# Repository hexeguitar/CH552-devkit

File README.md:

# CH552 devkit

### CH552 development board with hardware reboot into bootloader feature.  

### Reboot circuit  

Pressing and releasing the BOOTLOADER button will cycle the power and start the MCU with 1k pull-up on the USB-P line. This will start the built in USB/Serial bootoader. External BOOT input is provided for triggering via DTR or other active low signal.  

Take a look here for similar circuit for the CH559 series:  
https://github.com/hexeguitar/CH55x-HW-reboot  

Python programming script for both USB and serial port can be found here:  
https://github.com/hexeguitar/CH55x_python_flasher  
___
(c) 11.2020 by Piotr Zapart  
www.hexefx.com

[pic1]: pics/ch552_devkit1.jpg "CH552 devkit"
[pic2]: pics/ch552_devkit2.jpg "CH552 devkit"

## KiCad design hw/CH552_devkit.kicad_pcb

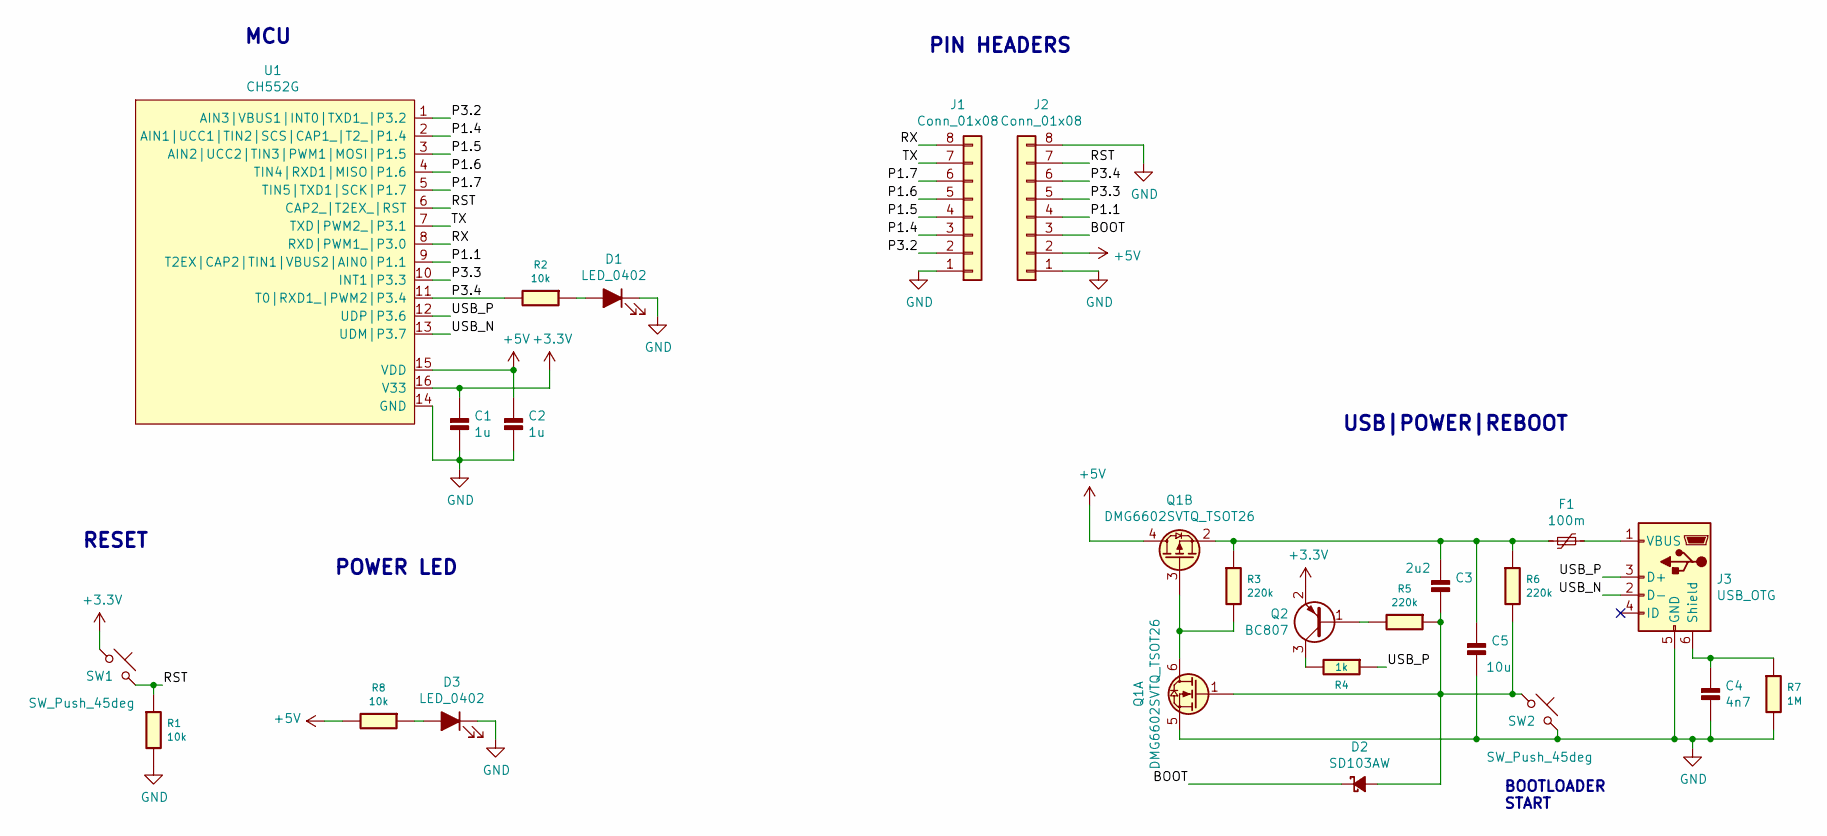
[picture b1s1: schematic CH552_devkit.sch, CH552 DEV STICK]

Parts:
C1, C2: 1u; Hx_C_0805_2012Metric
C3: 2u2; Hx_C_0805_2012Metric
C4: 4n7; Hx_C_0805_2012Metric
C5: 10u; Hx_C_0805_2012Metric
D1, D3: LED_0402; LED_0402_1005Metric
D2: SD103AW; D_SOD-123
F1: 100m; Fuse_1206_3216Metric
J1, J2: Conn_01x08; PinHeader_1x08_P2.54mm_Vertical
J3: USB_OTG; USB_Micro-B_Molex-105017-0001
Q1: DMG6602SVTQ_TSOT26; TSOT26
Q2: BC807; SOT-23
R1, R2, R8: 10k; Hx_R_0603_1608Metric
R3, R5, R6: 220k; Hx_R_0603_1608Metric
R4: 1k; Hx_R_0603_1608Metric
R7: 1M; Hx_R_1206_3216Metric
SW1, SW2: SW_Push_45deg; SW_Push_1P1T_NO_CK_KMR2
U1: CH552G; SOIC16

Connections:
+3V3: C1.1, Q2.2 (E), SW1.1, U1.16 (V33)
+5V: C2.1, J2.2, Q1.4 (D), R8.2, U1.15 (VDD)
/BOOT: D2.1 (K), J2.3
/P1.1: J2.4, U1.9 (T2EX|CAP2|TIN1|VBUS2|AIN0|P1.1)
/P1.4: J1.3, U1.2 (AIN1|UCC1|TIN2|SCS|CAP1_|T2_|P1.4)
/P1.5: J1.4, U1.3 (AIN2|UCC2|TIN3|PWM1|MOSI|P1.5)
/P1.6: J1.5, U1.4 (TIN4|RXD1|MISO|P1.6)
/P1.7: J1.6, U1.5 (TIN5|TXD1|SCK|P1.7)
/P3.2: J1.2, U1.1 (AIN3|VBUS1|INT0|TXD1_|P3.2)
/P3.3: J2.5, U1.10 (INT1|P3.3)
/P3.4: J2.6, R2.2, U1.11 (T0|RXD1_|PWM2|P3.4)
/RST: J2.7, R1.1, SW1.2, U1.6 (CAP2_|T2EX_|RST)
/RX: J1.8, U1.8 (RXD|PWM1_|P3.0)
/TX: J1.7, U1.7 (TXD|PWM2_|P3.1)
/USB_N: J3.2 (D-), U1.13 (UDM|P3.7)
/USB_P: J3.3 (D+), R4.1, U1.12 (UDP|P3.6)
GND: C1.2, C2.2, C4.2, C5.2, D1.1 (K), D3.1 (K), J1.1, J2.1, J2.8, J3.5 (GND), Q1.5 (S), R1.2, R7.2, SW2.2, U1.14 (GND)
unnamed: C3.1, C5.1, F1.2, Q1.2 (S), R3.1, R6.1
unnamed: C3.2, D2.2 (A), Q1.1 (G), R5.1, R6.2, SW2.1
unnamed: C4.1, J3.6 (Shield), R7.1
unnamed: D1.2 (A), R2.1
unnamed: D3.2 (A), R8.1
unnamed: F1.1, J3.1 (VBUS)
unnamed: Q1.3 (G), Q1.6 (D), R3.2
unnamed: Q2.1 (B), R5.2
unnamed: Q2.3 (C), R4.2

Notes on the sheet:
USB|POWER|REBOOT
PIN HEADERS
MCU
RESET
POWER LED
BOOTLOADER START

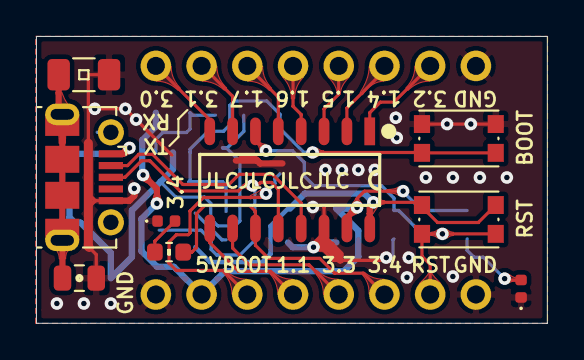
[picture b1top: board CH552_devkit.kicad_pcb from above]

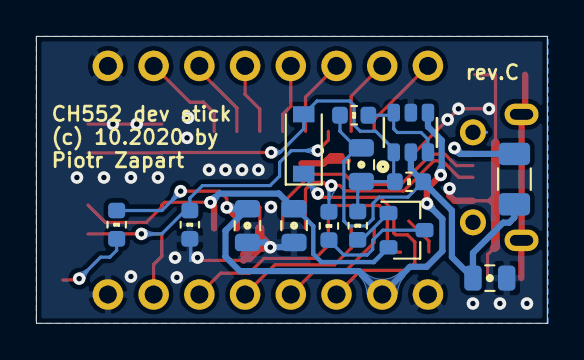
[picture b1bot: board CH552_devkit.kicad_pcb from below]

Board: 2 copper layers, 28.4 x 15.9 mm, 25 parts (14 on the bottom side), 26 nets.

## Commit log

2020-11-30 readme update
